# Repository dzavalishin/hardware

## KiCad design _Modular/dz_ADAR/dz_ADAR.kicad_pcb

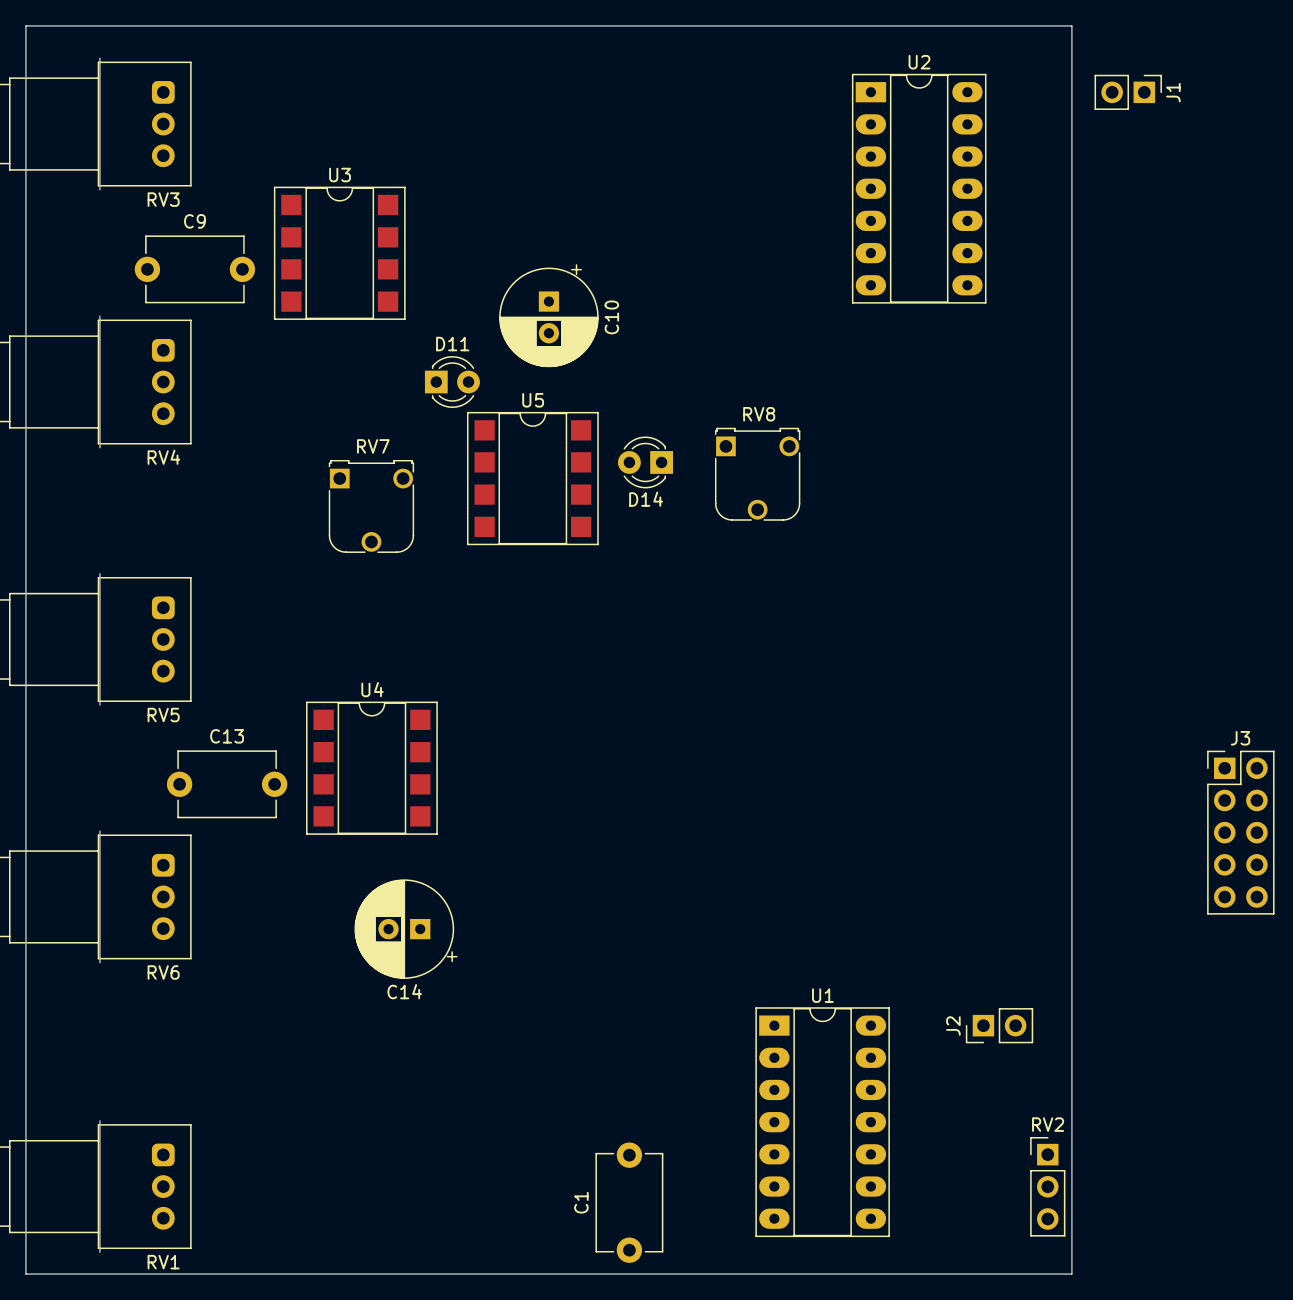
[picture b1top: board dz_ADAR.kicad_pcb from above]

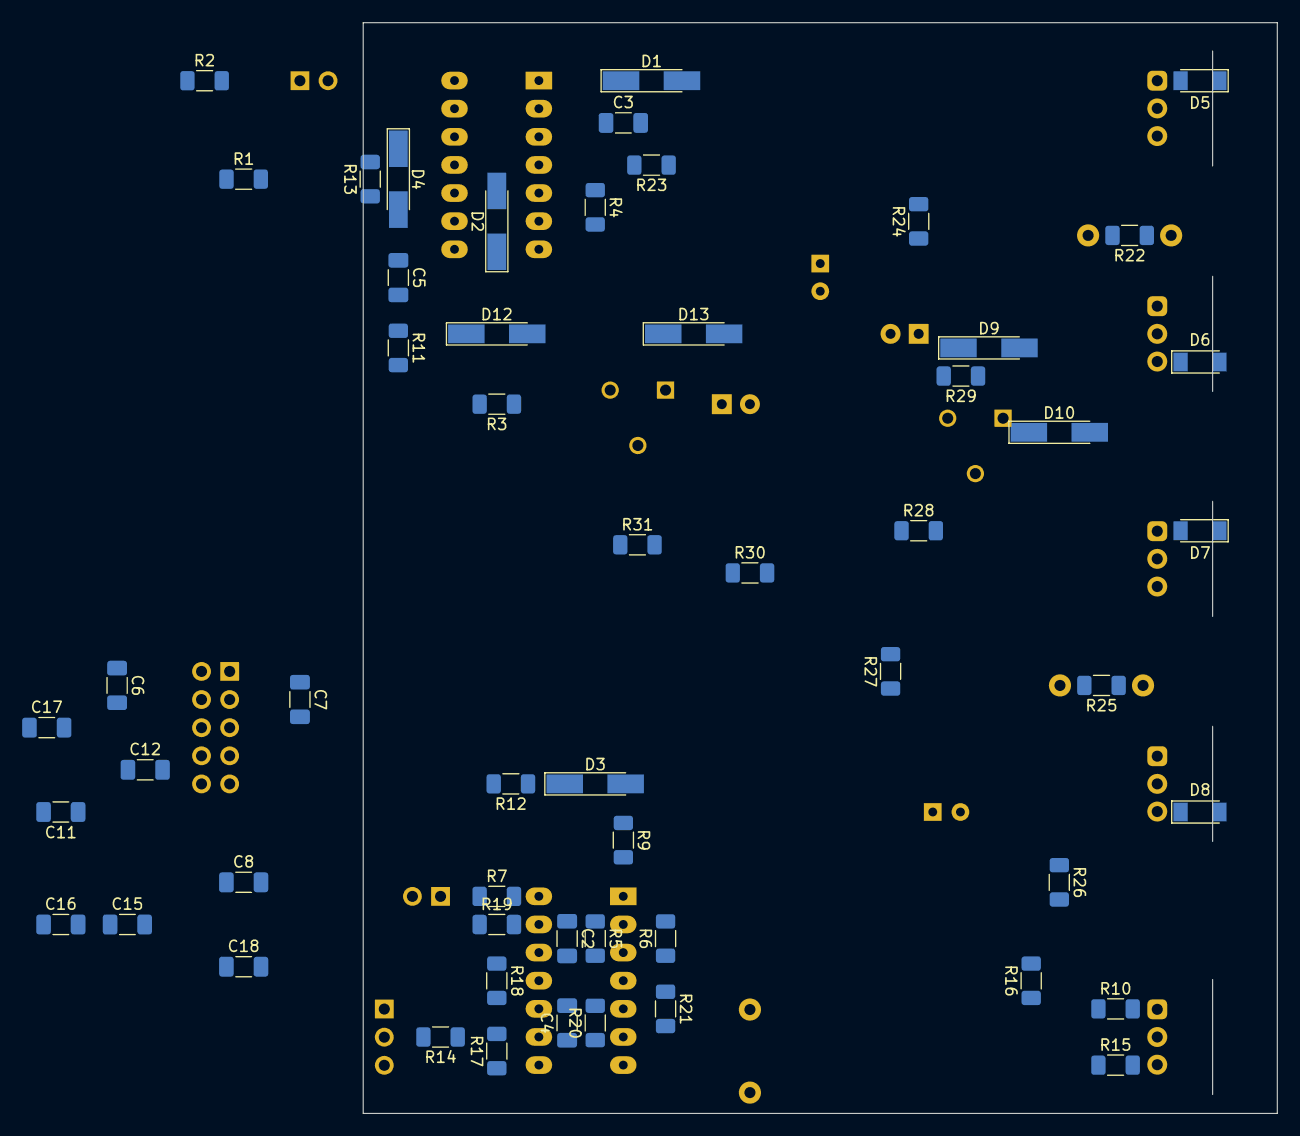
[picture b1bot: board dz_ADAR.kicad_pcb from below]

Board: 2 copper layers, 82.5 x 98.5 mm, 78 parts (55 on the bottom side), 50 nets, no tracks yet.

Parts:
C1, C9, C13: 100; C_Disc_D7.5mm_W5.0mm_P7.50mm
C2, C3, C4, C5, C6, C7, C8, C11, C12, C15, C16, C17, C18: 0,1; C_1206_3216Metric_Pad1.33x1.80mm_HandSolder
C10, C14: 20,0 x 35v; CP_Radial_D7.5mm_P2.50mm
D1, D2, D3, D4, D9, D10, D12, D13: D; D_MiniMELF_Handsoldering
D5, D6, D7, D8: LL4148; D_MiniMELF
D11, D14: LED_Dual_Bidirectional; LED_D3.0mm
J1: In; PinHeader_1x02_P2.54mm_Vertical
J2: Out; PinHeader_1x02_P2.54mm_Vertical
J3: Power; PinHeader_2x05_P2.54mm_Vertical
R1, R22, R25: 1m; R_1206_3216Metric_Pad1.30x1.75mm_HandSolder
R2, R3, R5, R9, R11, R21, R23, R26: 10k; R_1206_3216Metric_Pad1.30x1.75mm_HandSolder
R4, R12, R13, R16, R17, R18, R19, R28, R30: 100k; R_1206_3216Metric_Pad1.30x1.75mm_HandSolder
R6, R20: 2k; R_1206_3216Metric_Pad1.30x1.75mm_HandSolder
R7, R24, R27: 1k; R_1206_3216Metric_Pad1.30x1.75mm_HandSolder
R10, R14, R15: 50k; R_1206_3216Metric_Pad1.30x1.75mm_HandSolder
R29, R31: 5.1k; R_1206_3216Metric_Pad1.30x1.75mm_HandSolder
RV1: 100k; Potentiometer_Alps_RK097_Single_Horizontal
RV2: 100k; PinHeader_1x03_P2.54mm_Vertical
RV3, RV4, RV5, RV6: 1m; Potentiometer_Alps_RK097_Single_Horizontal
RV7, RV8: 100k; Potentiometer_Runtron_RM-065_Vertical
U1: TL084; DIP-14_W7.62mm_Socket_LongPads
U2: 4001; DIP-14_W7.62mm_Socket_LongPads
U3, U4, U5: TL072; DIP-8_W7.62mm_SMDSocket_SmallPads

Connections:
+2v: C4.1, R20.1, R21.2, U1.6 (-), U3.2 (-), U4.2 (-)
+12V: C6.1, C7.1, C11.2, C15.2, C17.1, D4.1 (K), J3.1, J3.2, R6.1, R13.2, R21.1, RV2.1, U1.4 (V+), U2.14 (VDD), U3.8 (V+), U4.8 (V+), U5.4 (V-)
-12V: C8.1, C10.2, C12.2, C14.2, C16.2, C18.1, J3.9, J3.10, RV2.3, U1.11 (V-), U3.4 (V-), U4.4 (V-), U5.8 (V+)
/AD/Gate: R23.2, U2.2, U2.4
/AD/Out: R24.1, R28.1, RV1.2, U1.3 (+), U3.6 (-)
/AR/Gate: C1.1, R1.1, R3.2, R11.2, R26.2, U1.7
/AR/Out: R16.2, R27.1, R30.1, U4.6 (-)
/In: J1.1, R2.2
GND: C2.2, C4.2, C6.2, C7.2, C8.2, C11.1, C12.1, C15.1, C16.1, C17.2, C18.2, D1.2 (A), J1.2, J2.2, J3.3, J3.4, J3.5, J3.6, J3.7, J3.8, R4.2, R5.2, R12.2, R20.2, R29.2, R31.2, U1.10 (+), U1.12 (+), U2.7 (VSS), U5.3 (+), U5.5 (+)
unnamed: C1.2, R1.2, R2.1, U1.5 (+)
unnamed: C2.1, R5.1, R6.2, U1.2 (-)
unnamed: C3.1, D1.1 (K), R4.1, U2.1
unnamed: C3.2, R3.1
unnamed: C5.1, D4.2 (A), R13.1, U2.8, U2.9
unnamed: C5.2, R11.1
unnamed: C9.1, R22.1, RV3.2, RV3.3, RV4.1, RV4.2, U3.1
unnamed: C9.2, R22.2, R23.1, U3.3 (+)
unnamed: C10.1, D5.1 (K), D6.2 (A), U3.5 (+)
unnamed: C13.1, R25.1, RV5.2, RV5.3, RV6.1, RV6.2, U4.1
unnamed: C13.2, R25.2, R26.1, U4.3 (+)
unnamed: C14.1, D7.1 (K), D8.2 (A), U4.5 (+)
unnamed: D2.1 (K), D3.1 (K), R12.1, U2.6
unnamed: D2.2 (A), U2.10
unnamed: D3.2 (A), R9.1
unnamed: D5.2 (A), RV3.1
unnamed: D6.1 (K), RV4.3
unnamed: D7.2 (A), RV5.1
unnamed: D8.1 (K), RV6.3
unnamed: D9.2 (A), RV7.3
unnamed: D10.1 (K), RV7.1
unnamed: D9.1 (K), D10.2 (A), D11.1 (KA), R29.1
unnamed: D11.2 (AK), U5.1
unnamed: D12.1 (K), D13.2 (A), D14.1 (KA), R31.1
unnamed: D12.2 (A), RV8.3
unnamed: D13.1 (K), RV8.1
unnamed: D14.2 (AK), U5.7
unnamed: R9.2, U1.1
unnamed: R10.1, R14.1, R16.1, R17.2, U1.9 (-)
unnamed: R10.2, RV1.1
unnamed: R14.2, RV2.2
unnamed: R15.1, R18.1, R19.2, U1.13 (-)
unnamed: R15.2, RV1.3
unnamed: R17.1, R18.2, U1.8
unnamed: J2.1, R7.1, R19.1
unnamed: R24.2, U3.7
unnamed: R27.2, U4.7
unnamed: R28.2, RV7.2, U5.2 (-)
unnamed: R30.2, RV8.2, U5.6 (-)
unnamed: R7.2, U1.14
unnamed: U2.3, U2.5

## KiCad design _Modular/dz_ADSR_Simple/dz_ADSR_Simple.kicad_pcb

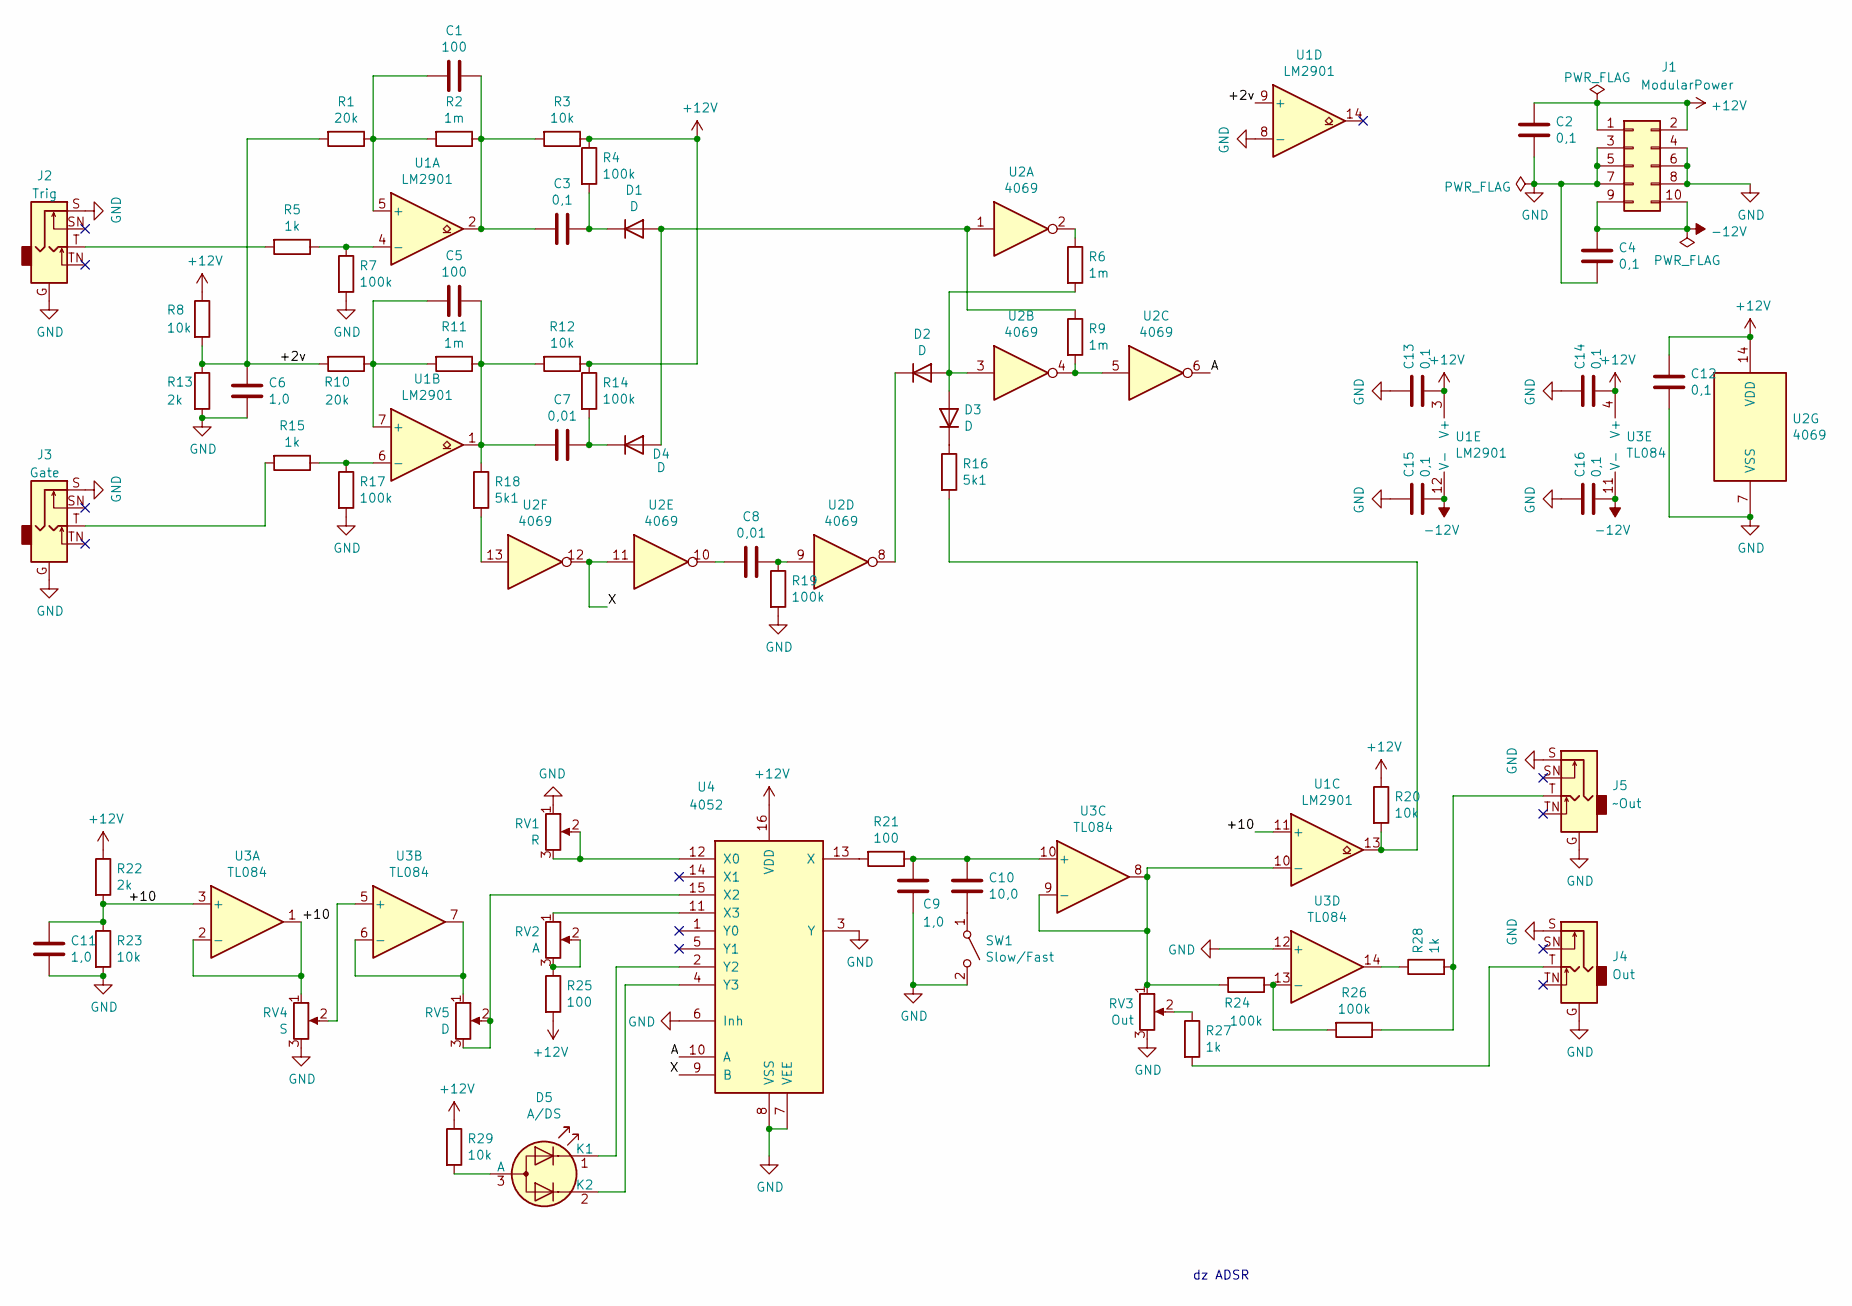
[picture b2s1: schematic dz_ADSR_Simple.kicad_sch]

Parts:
C1, C5: 100; C_0805_2012Metric_Pad1.18x1.45mm_HandSolder
C2, C3, C4, C12, C13, C14, C15, C16: 0,1; C_0805_2012Metric_Pad1.18x1.45mm_HandSolder
C6, C9, C11: 1,0; C_0805_2012Metric_Pad1.18x1.45mm_HandSolder
C7, C8: 0,01; C_0805_2012Metric_Pad1.18x1.45mm_HandSolder
C10: 10,0; C_0805_2012Metric_Pad1.18x1.45mm_HandSolder
D1, D2, D3, D4: D; D_MiniMELF_Handsoldering
D5: A/DS; LED_D3.0mm-3
J1: ModularPower; PinHeader_2x05_P2.54mm_Vertical
J2: Trig; Jack_3.5mm_CUI_SJ1-3525N_Horizontal
J3: Gate; Jack_3.5mm_CUI_SJ1-3525N_Horizontal
J4: Out; Jack_3.5mm_CUI_SJ1-3525N_Horizontal
J5: ~Out; Jack_3.5mm_CUI_SJ1-3525N_Horizontal
R1, R10: 20k; R_0805_2012Metric_Pad1.20x1.40mm_HandSolder
R2, R6, R9, R11: 1m; R_0805_2012Metric_Pad1.20x1.40mm_HandSolder
R3, R8, R12, R20, R23, R29: 10k; R_0805_2012Metric_Pad1.20x1.40mm_HandSolder
R4, R7, R14, R17, R19, R24, R26: 100k; R_0805_2012Metric_Pad1.20x1.40mm_HandSolder
R5, R15, R27, R28: 1k; R_0805_2012Metric_Pad1.20x1.40mm_HandSolder
R13, R22: 2k; R_0805_2012Metric_Pad1.20x1.40mm_HandSolder
R16, R18: 5k1; R_0805_2012Metric_Pad1.20x1.40mm_HandSolder
R21, R25: 100; R_0805_2012Metric_Pad1.20x1.40mm_HandSolder
RV1: R; Potentiometer_Bourns_3266W_Vertical
RV2: A; Potentiometer_Bourns_3266W_Vertical
RV3: Out; Potentiometer_Bourns_3266W_Vertical
RV4: S; Potentiometer_Bourns_3266W_Vertical
RV5: D; Potentiometer_Bourns_3266W_Vertical
SW1: Slow/Fast; PinHeader_1x02_P2.54mm_Vertical
U1: LM2901; DIP-14_W7.62mm_LongPads
U2: 4069; DIP-14_W7.62mm_LongPads
U3: TL084; DIP-14_W7.62mm_LongPads
U4: 4052; DIP-16_W7.62mm_LongPads

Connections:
+12V: C2.1, C12.1, C13.2, C14.2, J1.1, J1.2, R3.1, R4.1, R8.1, R12.1, R14.1, R20.1, R22.1, R25.2, R29.1, U1.3 (V+), U2.14 (VDD), U3.4 (V+), U4.16 (VDD)
-12V: C4.1, C15.2, C16.2, J1.9, J1.10, U1.12 (V-), U3.11 (V-)
/+2v: C6.2, R1.2, R8.2, R10.2, R13.1, U1.9 (+)
/+10: C11.1, R22.2, R23.1, RV4.1, U1.11 (+), U3.1, U3.2 (-), U3.3 (+)
/A: U2.6, U4.10 (A)
/X: U2.11, U2.12, U4.9 (B)
GND: C2.2, C4.2, C6.1, C9.2, C11.2, C12.2, C13.1, C14.1, C15.1, C16.1, J1.3, J1.4, J1.5, J1.6, J1.7, J1.8, J2.G, J2.S, J3.G, J3.S, J4.G, J4.S, J5.G, J5.S, R7.2, R13.2, R17.2, R19.2, R23.2, RV1.1, RV3.3, RV4.3, SW1.2 (B), U1.8 (-), U2.7 (VSS), U3.12 (+), U4.3 (Y), U4.6 (Inh), U4.7 (VEE), U4.8 (VSS)
unnamed: C1.1, C3.2, R2.1, R3.2, U1.2
unnamed: C1.2, R1.1, R2.2, U1.5 (+)
unnamed: C3.1, D1.1 (K), R4.2
unnamed: C5.1, C7.2, R11.1, R12.2, R18.1, U1.1
unnamed: C5.2, R10.1, R11.2, U1.7 (+)
unnamed: C7.1, D4.1 (K), R14.2
unnamed: C8.1, R19.1, U2.9
unnamed: C8.2, U2.10
unnamed: C9.1, C10.1, R21.1, U3.10 (+)
unnamed: C10.2, SW1.1 (A)
unnamed: D1.2 (A), D4.2 (A), R9.1, U2.1
unnamed: D2.1 (K), U2.8
unnamed: D2.2 (A), D3.2 (A), R6.2, U2.3
unnamed: D3.1 (K), R16.1
unnamed: D5.1 (K1), U4.2 (Y2)
unnamed: D5.2 (K2), U4.4 (Y3)
unnamed: D5.3 (A), R29.2
unnamed: J2.T, R5.2
unnamed: J3.T, R15.2
unnamed: J4.T, R27.2
unnamed: J5.T, R26.1, R28.2
unnamed: R5.1, R7.1, U1.4 (-)
unnamed: R6.1, U2.2
unnamed: R9.2, U2.4, U2.5
unnamed: R15.1, R17.1, U1.6 (-)
unnamed: R16.2, R20.2, U1.13
unnamed: R18.2, U2.13
unnamed: R21.2, U4.13 (X)
unnamed: R24.1, R26.2, U3.13 (-)
unnamed: R24.2, RV3.1, U1.10 (-), U3.8, U3.9 (-)
unnamed: R25.1, RV2.2, RV2.3
unnamed: R27.1, RV3.2
unnamed: R28.1, U3.14
unnamed: RV1.2, RV1.3, U4.12 (X0)
unnamed: RV2.1, U4.11 (X3)
unnamed: RV4.2, U3.5 (+)
unnamed: RV5.1, U3.6 (-), U3.7
unnamed: RV5.2, RV5.3, U4.15 (X2)

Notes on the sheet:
dz ADSR

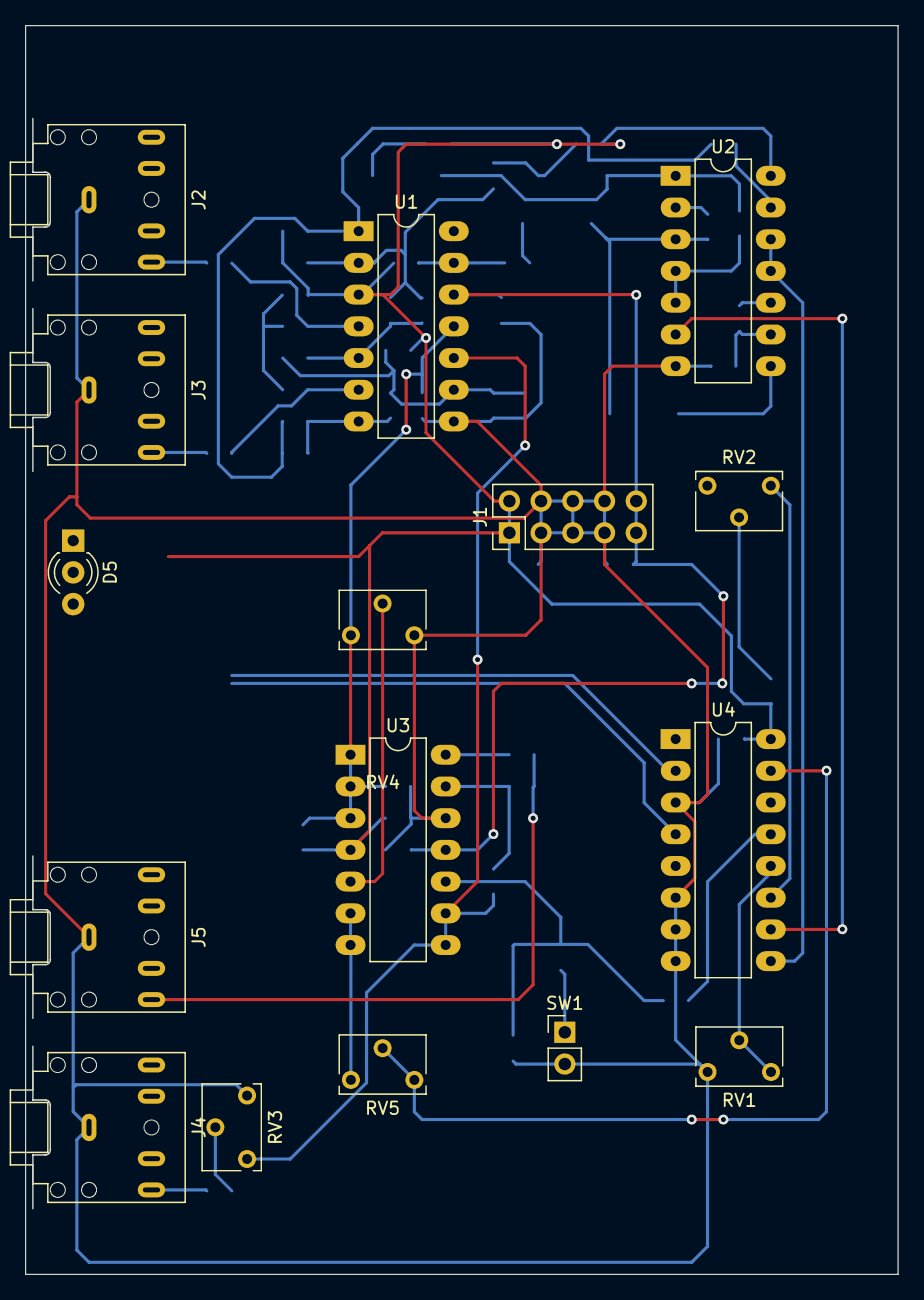
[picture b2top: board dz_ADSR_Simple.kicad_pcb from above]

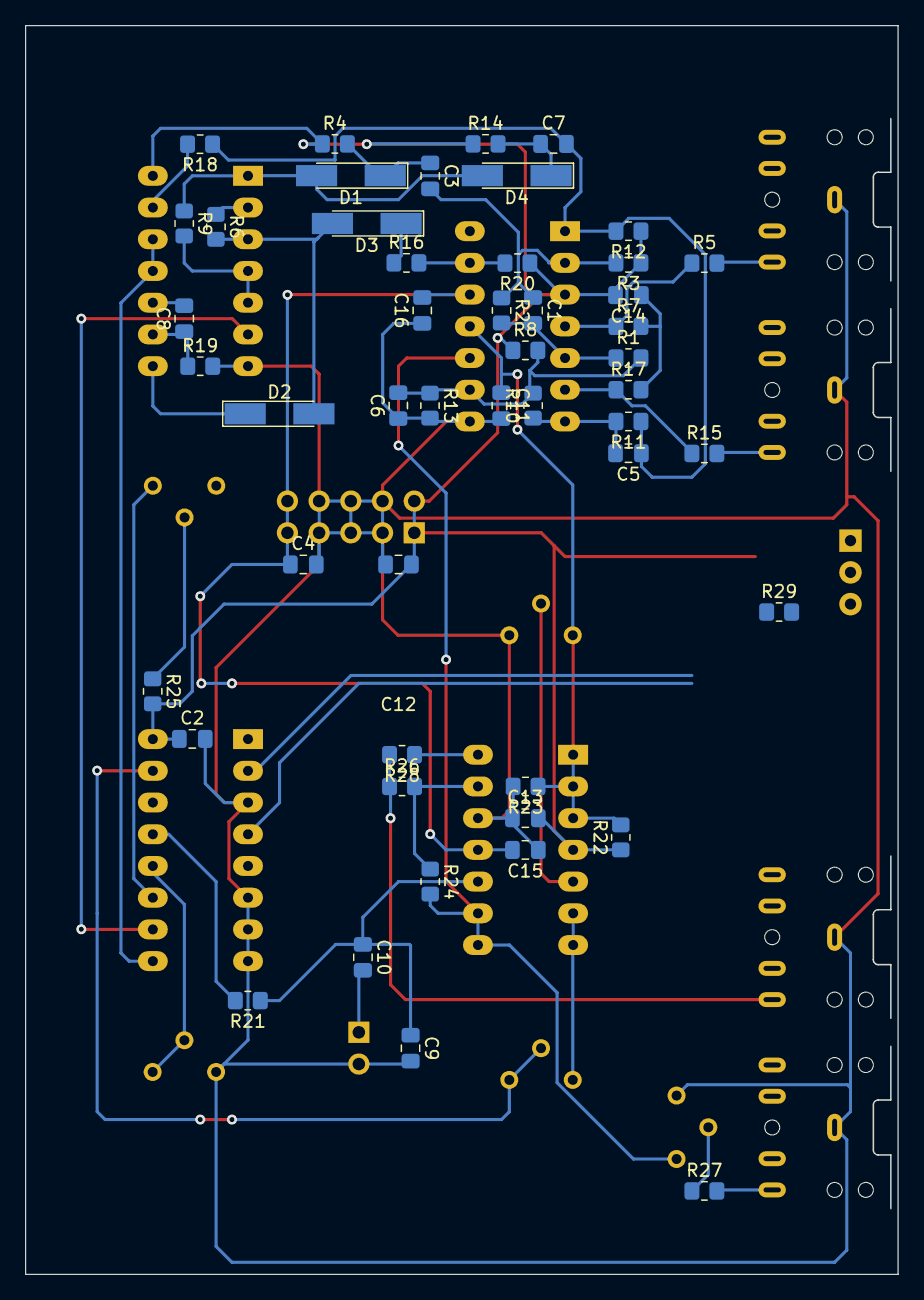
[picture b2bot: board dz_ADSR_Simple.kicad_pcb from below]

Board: 2 copper layers, 69.9 x 100.0 mm, 65 parts (49 on the bottom side), 45 nets.

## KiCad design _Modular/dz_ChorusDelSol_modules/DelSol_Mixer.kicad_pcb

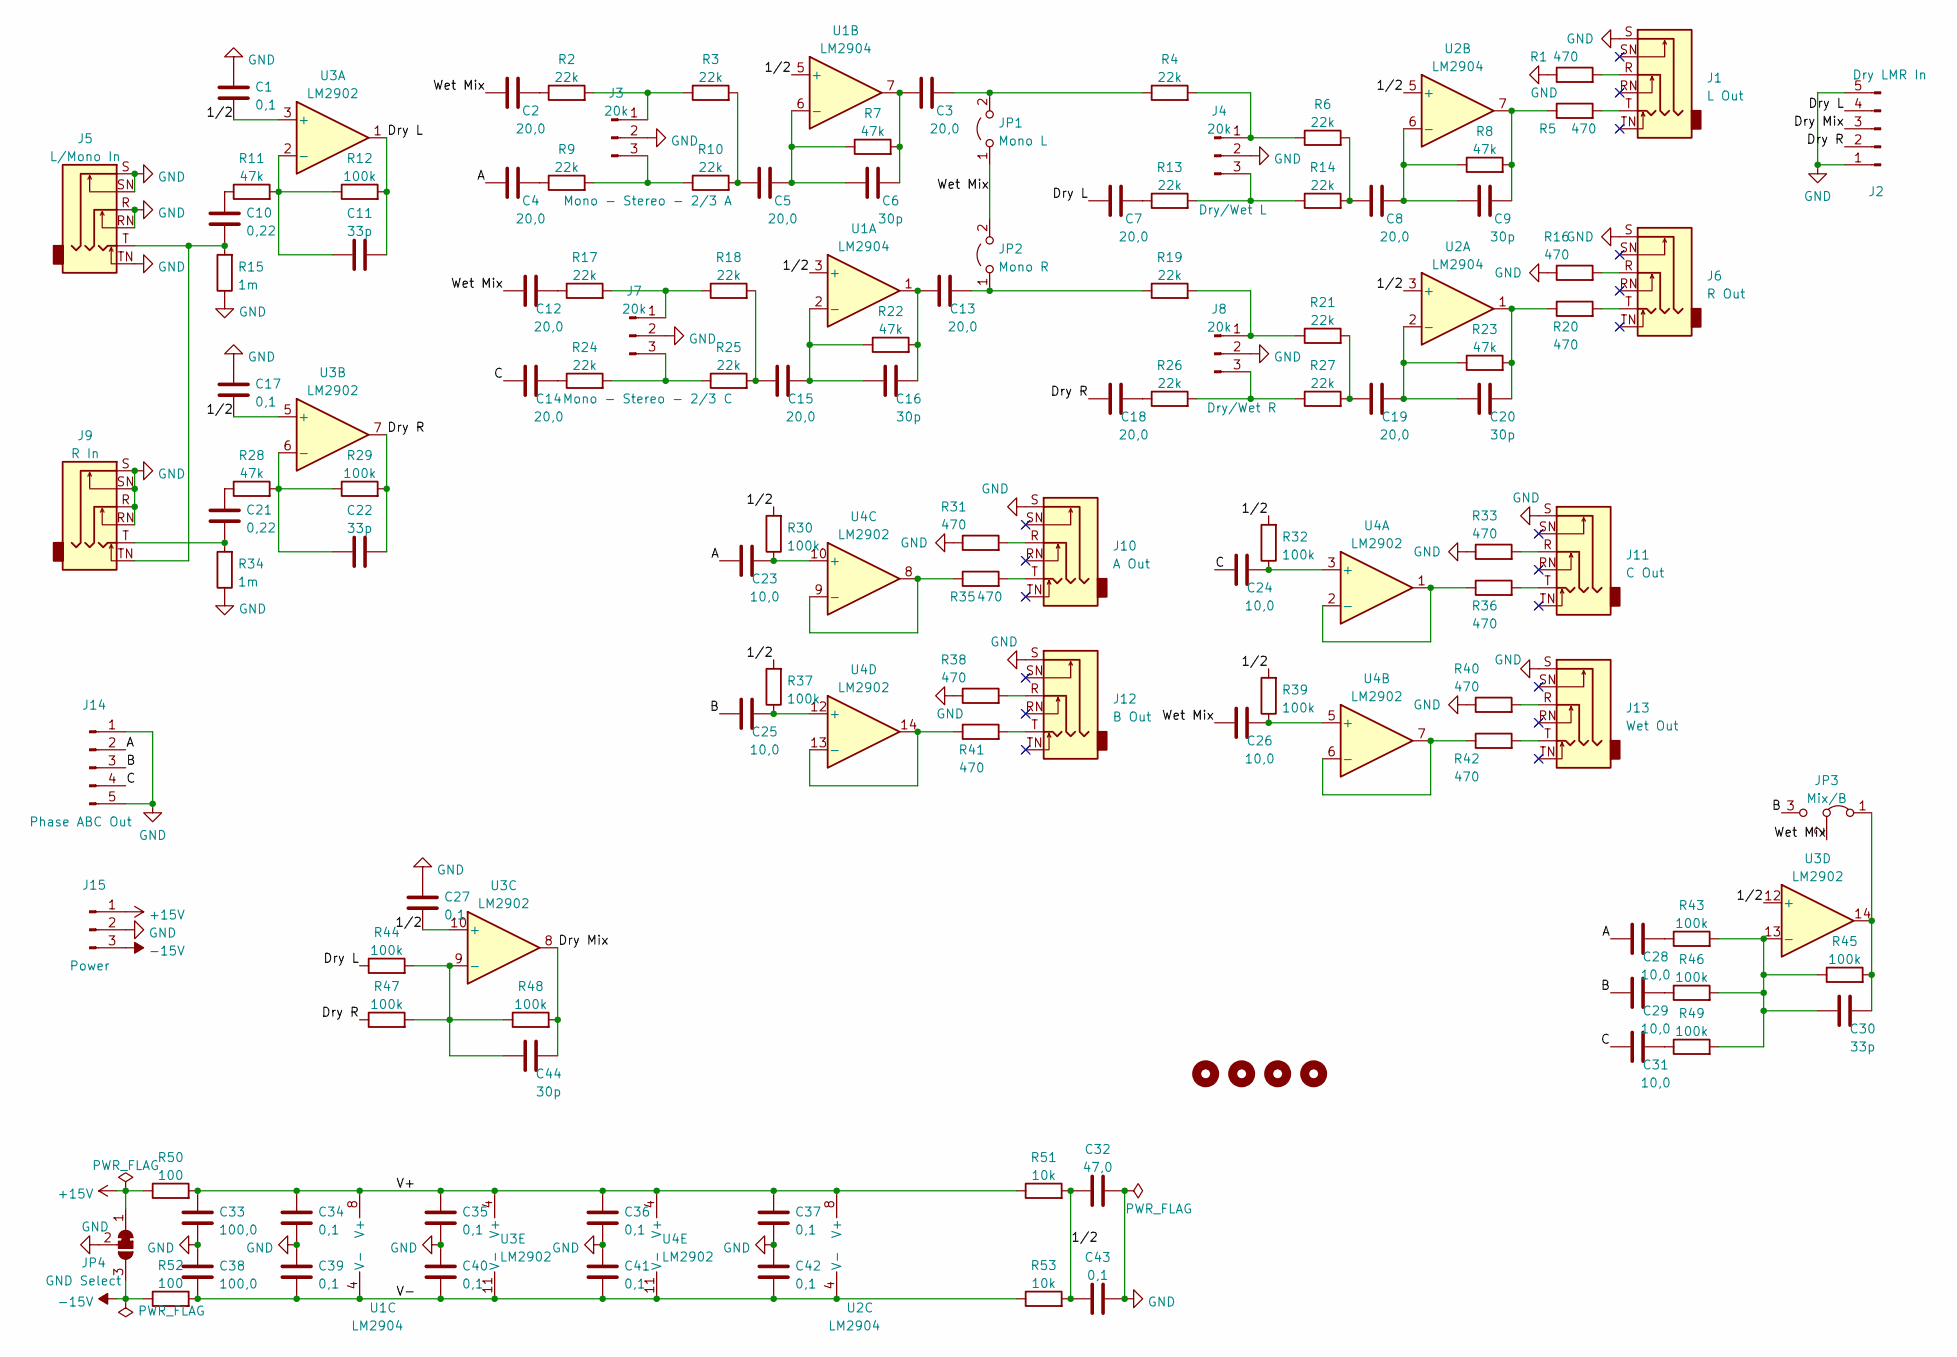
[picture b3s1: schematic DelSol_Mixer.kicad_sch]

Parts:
C1, C17, C27, C34, C35, C36, C37, C39, C40, C41, C42, C43: 0,1; C_1206_3216Metric_Pad1.33x1.80mm_HandSolder
C2, C3, C4, C5, C7, C8, C12, C13, C14, C15, C18, C19: 20,0; C_1206_3216Metric_Pad1.33x1.80mm_HandSolder
C6, C9, C16, C20, C44: 30p; C_Disc_D5.0mm_W2.5mm_P2.50mm
C10, C21: 0,22; C_0805_2012Metric_Pad1.18x1.45mm_HandSolder
C11, C22, C30: 33p; C_Disc_D5.0mm_W2.5mm_P2.50mm
C23, C24, C25, C26, C28, C29, C31: 10,0; C_0805_2012Metric_Pad1.18x1.45mm_HandSolder
C32: 47,0; C_Elec_6.3x5.8
C33, C38: 100,0; C_Elec_6.3x5.8
H1, H2, H3, H4: MountingHole; MountingHole_3.2mm_M3
J1: L Out; Jack_6.35mm_Neutrik_NMJ6HCD2_Horizontal
J2: Dry LMR In; PinHeader_1x05_P2.54mm_Vertical
J3, J4, J7, J8: 20k; PinHeader_1x03_P2.54mm_Vertical
J5: L/Mono In; Jack_6.35mm_Neutrik_NMJ6HCD2_Horizontal
J6: R Out; Jack_6.35mm_Neutrik_NMJ6HCD2_Horizontal
J9: R In; Jack_6.35mm_Neutrik_NMJ6HCD2_Horizontal
J10: A Out; Jack_6.35mm_Neutrik_NMJ6HCD2_Horizontal
J11: C Out; Jack_6.35mm_Neutrik_NMJ6HCD2_Horizontal
J12: B Out; Jack_6.35mm_Neutrik_NMJ6HCD2_Horizontal
J13: Wet Out; Jack_6.35mm_Neutrik_NMJ6HCD2_Horizontal
J14: Phase ABC Out; PinHeader_1x05_P2.54mm_Vertical
J15: Power; PinHeader_1x03_P2.54mm_Vertical
JP1: Mono L; PinHeader_1x02_P2.54mm_Vertical
JP2: Mono R; PinHeader_1x02_P2.54mm_Vertical
JP3: Mix/B; PinHeader_1x03_P2.54mm_Vertical
JP4: GND Select; PinHeader_1x03_P2.54mm_Vertical
R1, R5, R16, R20, R31, R33, R35, R36, R38, R40, R41, R42: 470; R_1206_3216Metric_Pad1.30x1.75mm_HandSolder
R2, R3, R4, R6, R9, R10, R13, R14, R17, R18, R19, R21, R24, R25, R26, R27: 22k; R_1206_3216Metric_Pad1.30x1.75mm_HandSolder
R7, R8, R11, R22, R23, R28: 47k; R_1206_3216Metric_Pad1.30x1.75mm_HandSolder
R12, R29, R30, R32, R37, R39, R43, R44, R45, R46, R47, R48, R49: 100k; R_1206_3216Metric_Pad1.30x1.75mm_HandSolder
R15, R34: 1m; R_1206_3216Metric_Pad1.30x1.75mm_HandSolder
R50, R52: 100; R_1206_3216Metric_Pad1.30x1.75mm_HandSolder
R51, R53: 10k; R_1206_3216Metric_Pad1.30x1.75mm_HandSolder
U1, U2: LM2904; DIP-8_W7.62mm
U3, U4: LM2902; DIP-14_W7.62mm

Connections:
+15V: J15.1, JP4.1 (A), R50.1
-15V: J15.3, JP4.3 (B), R52.1
/1/2: C1.2, C17.2, C27.2, C32.1, C43.1, R30.2, R32.2, R37.2, R39.2, R51.2, R53.2, U1.3 (+), U1.5 (+), U2.3 (+), U2.5 (+), U3.3 (+), U3.5 (+), U3.10 (+), U3.12 (+)
/A: C4.1, C23.1, C28.1, J14.2
/B: C25.1, C29.1, J14.3, JP3.3 (B)
/C: C14.1, C24.1, C31.1, J14.4
/Dry L: C7.1, C11.2, J2.4, R12.2, R44.1, U3.1
/Dry Mix: C44.2, J2.3, R48.2, U3.8
/Dry R: C18.1, C22.2, J2.2, R29.2, R47.1, U3.7
/V+: C33.1, C34.1, C35.1, C36.1, C37.1, R50.2, R51.1, U1.8 (V+), U2.8 (V+), U3.4 (V+), U4.4 (V+)
/V-: C38.2, C39.2, C40.2, C41.2, C42.2, R52.2, R53.1, U1.4 (V-), U2.4 (V-), U3.11 (V-), U4.11 (V-)
/Wet Mix: C2.1, C12.1, C26.1, JP1.1 (A), JP2.2 (B), JP3.2 (C)
GND: C1.1, C17.1, C27.1, C32.2, C33.2, C34.2, C35.2, C36.2, C37.2, C38.1, C39.1, C40.1, C41.1, C42.1, C43.2, J1.S, J2.1, J2.5, J3.2, J4.2, J5.R, J5.RN, J5.S, J5.SN, J5.TN, J6.S, J7.2, J8.2, J9.R, J9.RN, J9.S, J9.SN, J10.S, J11.S, J12.S, J13.S, J14.1, J14.5, J15.2, JP4.2 (C), R1.1, R15.1, R16.1, R31.1, R33.1, R34.1, R38.1, R40.1
unnamed: C2.2, R2.1
unnamed: C3.1, C6.2, R7.2, U1.7
unnamed: C3.2, JP1.2 (B), R4.1
unnamed: C4.2, R9.1
unnamed: C5.1, R3.2, R10.2
unnamed: C5.2, C6.1, R7.1, U1.6 (-)
unnamed: C7.2, R13.1
unnamed: C8.1, R6.2, R14.2
unnamed: C8.2, C9.1, R8.1, U2.6 (-)
unnamed: C9.2, R5.1, R8.2, U2.7
unnamed: C10.1, R11.1
unnamed: C10.2, J5.T, J9.TN, R15.2
unnamed: C11.1, R11.2, R12.1, U3.2 (-)
unnamed: C12.2, R17.1
unnamed: C13.1, C16.2, R22.2, U1.1
unnamed: C13.2, JP2.1 (A), R19.1
unnamed: C14.2, R24.1
unnamed: C15.1, R18.2, R25.2
unnamed: C15.2, C16.1, R22.1, U1.2 (-)
unnamed: C18.2, R26.1
unnamed: C19.1, R21.2, R27.2
unnamed: C19.2, C20.1, R23.1, U2.2 (-)
unnamed: C20.2, R20.1, R23.2, U2.1
unnamed: C21.1, R28.1
unnamed: C21.2, J9.T, R34.2
unnamed: C22.1, R28.2, R29.1, U3.6 (-)
unnamed: C23.2, R30.1, U4.10 (+)
unnamed: C24.2, R32.1, U4.3 (+)
unnamed: C25.2, R37.1, U4.12 (+)
unnamed: C26.2, R39.1, U4.5 (+)
unnamed: C28.2, R43.1
unnamed: C29.2, R46.1
unnamed: C30.1, R43.2, R45.1, R46.2, R49.2, U3.13 (-)
unnamed: C30.2, JP3.1 (A), R45.2, U3.14
unnamed: C31.2, R49.1
unnamed: J1.R, R1.2
unnamed: J1.T, R5.2
unnamed: J3.1, R2.2, R3.1
unnamed: J3.3, R9.2, R10.1
unnamed: J4.1, R4.2, R6.1
unnamed: J4.3, R13.2, R14.1
unnamed: J6.R, R16.2
unnamed: J6.T, R20.2
unnamed: J7.1, R17.2, R18.1
unnamed: J7.3, R24.2, R25.1
unnamed: J8.1, R19.2, R21.1
unnamed: J8.3, R26.2, R27.1
unnamed: J10.R, R31.2
unnamed: J10.T, R35.2
unnamed: J11.R, R33.2
unnamed: J11.T, R36.2
unnamed: J12.R, R38.2
unnamed: J12.T, R41.2
unnamed: J13.R, R40.2
unnamed: J13.T, R42.2
unnamed: R35.1, U4.8, U4.9 (-)
unnamed: R36.1, U4.1, U4.2 (-)
unnamed: R41.1, U4.13 (-), U4.14
unnamed: R42.1, U4.6 (-), U4.7
unnamed: C44.1, R44.2, R47.2, R48.1, U3.9 (-)

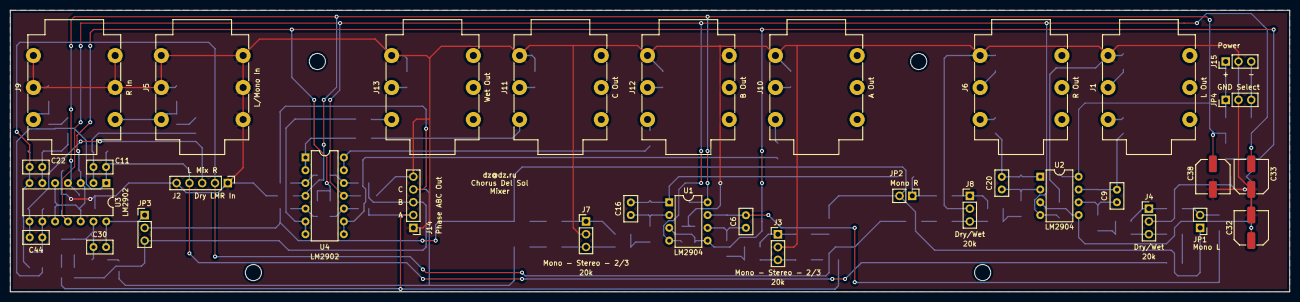
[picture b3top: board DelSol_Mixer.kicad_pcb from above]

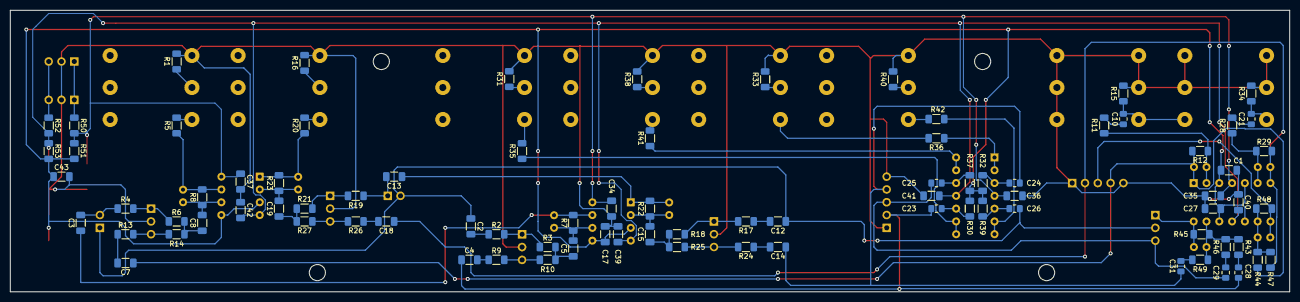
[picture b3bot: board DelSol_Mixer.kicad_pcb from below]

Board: 2 copper layers, 254.0 x 55.9 mm, 124 parts (86 on the bottom side), 73 nets.

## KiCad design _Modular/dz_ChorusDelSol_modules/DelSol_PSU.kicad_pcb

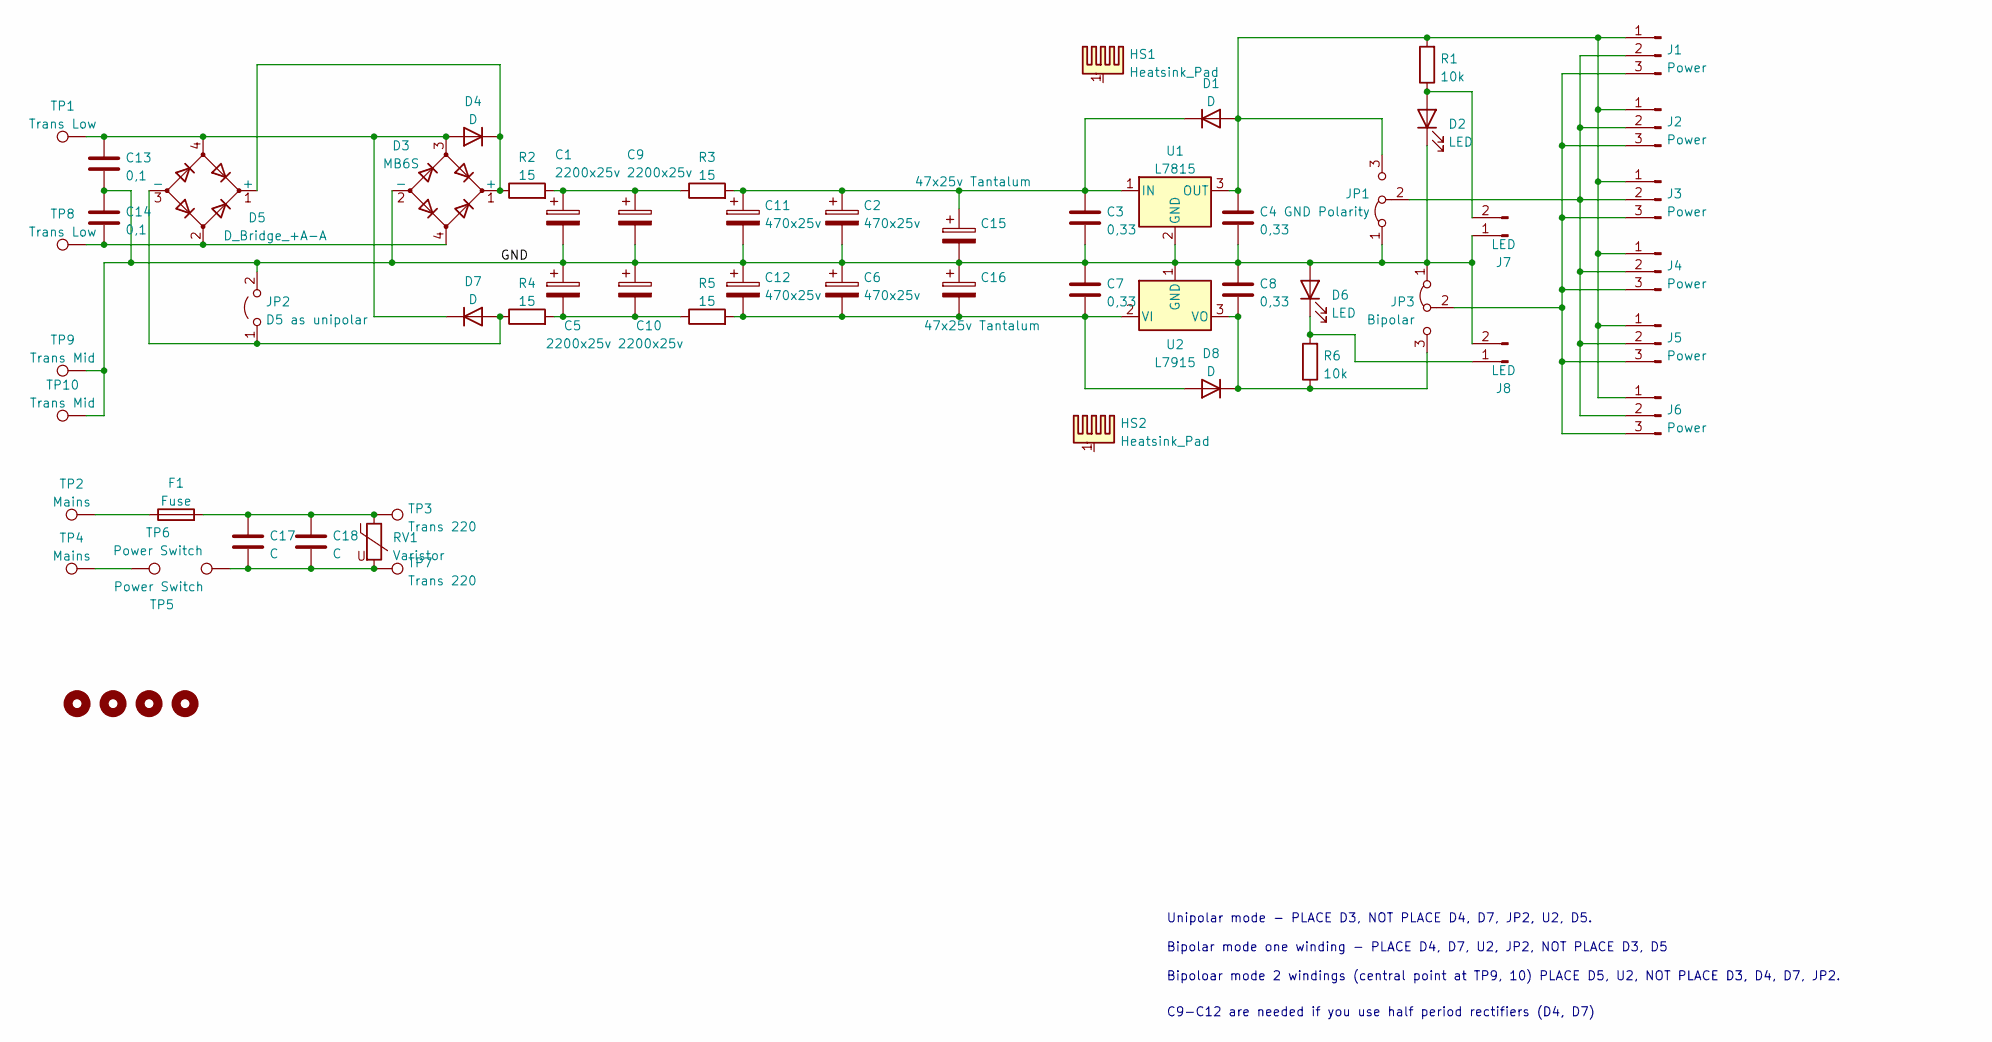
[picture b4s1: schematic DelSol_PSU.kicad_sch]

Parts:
C1, C5, C9, C10: 2200x25v; CP_Radial_D13.0mm_P5.00mm
C2, C6, C11, C12: 470x25v; CP_Radial_D13.0mm_P5.00mm
C3, C4, C7, C8: 0,33; C_0805_2012Metric_Pad1.18x1.45mm_HandSolder
C13, C14: 0,1; C_0805_2012Metric_Pad1.18x1.45mm_HandSolder
C15, C16: 47x25v Tantalum; CP_EIA-2012-12_Kemet-R_Pad1.30x1.05mm_HandSolder
C17, C18: C; C_Axial_L12.0mm_D6.5mm_P20.00mm_Horizontal
D1, D4, D7, D8: D; D_SMA-SMB_Universal_Handsoldering
D2, D6: LED; LED_1206_3216Metric_Pad1.42x1.75mm_HandSolder
D3: MB6S; Diode_Bridge_OnSemi_SDIP-4L
D5: D_Bridge_+A-A; Diode_Bridge_Round_D9.0mm
F1: Fuse; Fuseholder_Clip-5x20mm_Keystone_3512_Inline_P23.62x7.27mm_D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
H1, H2, H3, H4: MountingHole; MountingHole_3.2mm_M3
HS1, HS2: Heatsink_Pad; Heatsink_AAVID_576802B03900G
J1, J2, J3, J4, J5, J6: Power; PinHeader_1x03_P2.54mm_Vertical
J7, J8: LED; PinHeader_1x02_P2.54mm_Vertical
JP1: GND Polarity; PinHeader_1x03_P2.54mm_Vertical
JP2: D5 as unipolar; TestPoint_2Pads_Pitch2.54mm_Drill0.8mm
JP3: Bipolar; PinHeader_1x03_P2.54mm_Vertical
R1, R6: 10k; R_1206_3216Metric_Pad1.30x1.75mm_HandSolder
R2, R3, R4, R5: 15; R_Axial_DIN0516_L15.5mm_D5.0mm_P5.08mm_Vertical
RV1: Varistor; RV_Disc_D15.5mm_W3.9mm_P7.5mm
TP1, TP8: Trans Low; TestPoint_THTPad_2.0x2.0mm_Drill1.0mm
TP2, TP4: Mains; TestPoint_THTPad_2.0x2.0mm_Drill1.0mm
TP3, TP7: Trans 220; TestPoint_THTPad_2.0x2.0mm_Drill1.0mm
TP5, TP6: Power Switch; TestPoint_THTPad_2.0x2.0mm_Drill1.0mm
TP9, TP10: Trans Mid; TestPoint_THTPad_2.0x2.0mm_Drill1.0mm
U1: L7815; TO-220-3_Vertical
U2: L7915; TO-220-3_Vertical

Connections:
/GND: C1.2, C2.2, C3.2, C4.2, C5.1, C6.1, C7.1, C8.1, C9.2, C10.1, C11.2, C12.1, C13.2, C14.1, C15.2, C16.1, D2.1 (K), D3.2 (-), D6.2 (A), J7.1, J8.2, JP1.1 (A), JP2.2 (B), JP3.1 (A), TP9.1, TP10.1, U1.2 (GND), U2.1 (GND)
unnamed: C1.1, C9.1, R2.2, R3.1
unnamed: C2.1, C3.1, C11.1, C15.1, D1.1 (K), R3.2, U1.1 (IN)
unnamed: C4.1, D1.2 (A), J1.1, J2.1, J3.1, J4.1, J5.1, J6.1, JP1.3 (B), R1.2, U1.3 (OUT)
unnamed: C5.2, C10.2, R4.2, R5.1
unnamed: C6.2, C7.2, C12.2, C16.2, D8.2 (A), R5.2, U2.2 (VI)
unnamed: C8.2, D8.1 (K), JP3.3 (B), R6.1, U2.3 (VO)
unnamed: D2.2 (A), J7.2, R1.1
unnamed: D3.1 (+), D4.1 (K), D5.1 (+), R2.1
unnamed: C13.1, D3.3, D4.2 (A), D5.4, D7.1 (K), TP1.1
unnamed: C14.2, D3.4, D5.2, TP8.1
unnamed: D5.3 (-), D7.2 (A), JP2.1 (A), R4.1
unnamed: D6.1 (K), J8.1, R6.2
unnamed: F1.1, TP2.1
unnamed: C17.1, C18.1, F1.2, RV1.1, TP3.1
unnamed: J1.2, J2.2, J3.2, J4.2, J5.2, J6.2, JP1.2 (C)
unnamed: J1.3, J2.3, J3.3, J4.3, J5.3, J6.3, JP3.2 (C)
unnamed: TP4.1, TP5.1
unnamed: C17.2, C18.2, RV1.2, TP6.1, TP7.1

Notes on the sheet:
Unipolar mode - PLACE D3, NOT PLACE D4, D7, JP2, U2, D5. Bipolar mode one winding - PLACE D4, D7, U2, JP2, NOT PLACE D3, D5 Bipoloar mode 2 windings (central point at TP9, 10) PLACE D5, U2, NOT PLACE D3, D4, D7, JP2.
C9-C12 are needed if you use half period rectifiers (D4, D7)
